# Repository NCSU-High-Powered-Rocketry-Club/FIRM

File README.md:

# FIRM

Filtered Inertial Rotation Module

FIRM is a project by the NCSU High Powered Rocketry Club to develop a flight computer for high powered rockets. The flight computer is designed to provide accurate attitude and position data during flight using an array of sensors and an error-state Kalman filter.

It is also designed to be modular and easily adaptable to different rocket configurations and mission requirements. The project includes a custom PCB that integrates the sensors and microcontroller into a compact, lightweight package suitable for high-speed flight.

This repository holds the STM32 firmware (written in C), a USB client (Rust, with Python and TypeScript bindings) that interfaces with the hardware, a React web app for Web Serial configuration, MkDocs documentation, and post-flight processing tools for log archives, ESKF replay, and trace analysis.

## Layout

| Path           | What it is                                                                   |
|----------------|------------------------------------------------------------------------------|
| `STM32/`       | Firmware (CubeMX / VS Code STM32 extension)                                  |
| `client/`      | USB client crates, `firm-client` Python bindings, and WASM/TypeScript client |
| `web/`         | React web app (Web Serial UI); depends on the local `client/` package        |
| `docs/`        | MkDocs documentation (Material theme), built from `mkdocs.yaml`              |
| `processing/`  | Offline tools: `firm-hprc` (`firm.flight_data`, `firm.eskf_lab`)             |
| `flight_data/` | Versioned flight-log archive (data only)                                     |
| `tests/`       | Pytest and protocol C checks (firmware unit tests live in `STM32/tests/`)    |

## Setup

Install [uv](https://docs.astral.sh/uv/), Rust, CMake, Ninja, a host C compiler, and [just](https://github.com/casey/just). Building the firmware (`just build`, `just build-firmware`, `just ci`) also needs the ARM GNU toolchain (`arm-none-eabi-gcc`) on your `PATH`. It comes with [STM32CubeCLT](https://www.st.com/en/development-tools/stm32cubeclt.html) (see [STM32/README.md](STM32/README.md)), or you can install the [Arm GNU Toolchain](https://developer.arm.com/downloads/-/arm-gnu-toolchain-downloads) directly (CI uses 13.3.Rel1).

`just` is a command runner, so every `just <recipe>` below needs it on your `PATH`. Once uv is installed, the easiest way to get it on any OS is:

```bash
uv tool install rust-just
```

Other options are `brew install just` (macOS), `winget install Casey.Just` (Windows), or `cargo install just`. See the [just install docs](https://just.systems/man/en/packages.html) for more.

Clone the repo and sync Python packages:

```bash
git clone https://github.com/NCSU-High-Powered-Rocketry-Club/FIRM.git
cd FIRM
just sync
```

`just sync` installs `firm-hprc` and `firm-client` into your `.venv`.

## Commands

```bash
just build          # firmware Debug ELF + native ESKF and C tests + cargo
just build-eskf     # only the native ESKF replay tool
just test           # CTest + cargo + pytest, excluding integration (summary at the end)
just lint           # ruff, rustfmt, clippy, clang-format
just ci             # local firmware/C tests/rust/python/lint
just publish        # PyPI + npm + crates.io (see `just dry_run=true publish`)
just --list         # list all just recipes including building/testing/linting individual targets
```

## Web app and docs

The React app in `web/` talks to FIRM over Web Serial and uses the local WASM client (`firm-client` from `client/`; the root `package.json` makes `client/` and `web/` one npm workspace). The MkDocs site lives in `docs/`. The app needs [Node.js](https://nodejs.org/) (version in `.nvmrc`) and `wasm-pack` (so `client/` can compile its WASM package); docs need only uv.

```bash
just sync-web       # npm ci for the workspace; builds client WASM + TypeScript (once, and after dependency changes)
just web-dev        # Vite dev server for the web app (http://localhost:5173/)
just build-web      # production build of the React app
just lint-web       # ESLint and Prettier over client/ and web/, tsc over web/
just build-docs     # MkDocs site to ./site/
```

`just web-dev` runs `npm run dev -w web`. `just build-docs` writes the static site to `site/`; `uv run --group docs mkdocs serve` serves it at http://127.0.0.1:8000/docs/. Production is https://firm.ncsurocketry.org/ (app) and https://firm.ncsurocketry.org/docs/ (docs). See [web/README.md](web/README.md).

## Processing tools

After running `just sync`:

```bash
uv run firm-log --help
uv run firm-eskf --help
uv run firm-trace --help
uv run firm-reconstruct --help
```

For live USB data from a connected FIRM, use `firm_client.FIRMClient`. See [client/README.md](client/README.md).

## Hardware

| Part Number   | Description          | Datasheet                                                                                                   |
|---------------|----------------------|-------------------------------------------------------------------------------------------------------------|
| ICM-45686     | 6 Axis IMU           | [Datasheet](https://www.mouser.com/catalog/specsheets/TDK_DS_000577_ICM_45686.pdf)                          |
| STM32F405RGT6 | Microcontroller      | [Datasheet](https://www.st.com/resource/en/datasheet/dm00037051.pdf)                                        |
| MMC5983MA     | Magnetometer         | [Datasheet](https://media.digikey.com/pdf/Data%20Sheets/MEMSIC%20PDFs/MMC5983MA_RevA_4-3-19.pdf)            |
| BMP581        | Pressure Sensor      | [Datasheet](https://www.bosch-sensortec.com/media/boschsensortec/downloads/datasheets/bst-bmp581-ds004.pdf) |
| ADXL371       | High-g Accelerometer | [Datasheet](https://www.analog.com/media/en/technical-documentation/data-sheets/adxl371.pdf)                |
| W25Q128JV     | 128 Mbit SPI Flash   | [Datasheet](https://www.winbond.com/resource-files/w25q128jv%20revf%2003272018%20plus.pdf)                  |

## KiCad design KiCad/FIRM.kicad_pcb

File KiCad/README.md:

# FIRM PCB
This README aims to explain the hardware of FIRM in-depth and explain the design choices that went into designing our board.

## Overview

The purpose of creating our own PCB for FIRM was for a few main reasons. A big reason is customizabiltiy. When creating a flight controller from breakout boards, we are largely limited by the breakout boards that are supplied by major hobbyist companies like Adafruit and Sparkfun. A second reason is size. It's no surprise that when you only buy the sensor itself and not the entire breakout board, you can save a lot of wasted space that otherwise would be taken up by standard 0.1 inch pitch pinouts. The last major reason is cost. Hobbyist companies put huge mark-ups on their breakout boards, so we save a lot of money by designing and ordering the boards ourselves.

The schematic design is split up into 4 major components:
- Microcontroller: The heart of the board, supplies all of our pinouts and programmed to interface with the sensors
- Sensors: The hardware units that read pressure, temperature, acceleration, angular rate, magnetic field, etc.
- Logging/Storage: Encompasses our flash chip and the microSD card socket
- Power: The power input for the board through either input pins or USB, as well as the voltage regulator

## Microcontroller

Our MCU is the STM32F405RGT6. The name of this chip tells us a lot of information about it:

- "STM32": This is the 32-bit MCU family. The other main example is STM8 for 8-bit MCUs.
- "F": The type of the MCU, F is for foundational, sometimes high-performance though. Thier naming scheme isn't super consistant. Other common ones are G for mainstream, L for low-power, H for high-performance, and W for wireless.
- "4": The core, specifies the ARM Cortex chip used. STM32F4 MCU's use an ARM Cortex M4.
- "05": One of the models in the STM32F4 product lineup
- "R": Number of pinouts on the MCU. R either means 64 or 66. In our case, we have 64 pinouts.
- "G": Flash memory size, we have 1024 KBytes.
- "T": Package type, T is for LQFP packages.
- "6": Temperature rating, 6 denotes -40\deg C to 105\deg C.
[Heres a guide with more information about the naming scheme](https://www.digikey.com/en/maker/tutorials/2020/understanding-stm32-naming-conventions)

The main reason we chose this MCU in particular was due to its popularity, namely in drone flight controllers. We decided that having an MCU that was well-documented was going to be more important than an MCU that had the best specs. While specs do matter, we started this project with no STM32 experience and we knew development would go faster when there's already someone online that has encountered (and fixed) all the issues we run into.

The pinouts are also important for the MCU. We wanted to communicate through our sensors through SPI, which is much faster than the alternative communication protocol, I2C. Another supported protocol is UART, which will be used (in future FIRM iterations) for GPS, and also can be used for communicating with a main device such as an Arduino so that FIRM can transmit flight data real-time to it. It is important to note that many of the pins have alternate uses and can be configred via STM32CubeMX to do different functions.

## Sensors

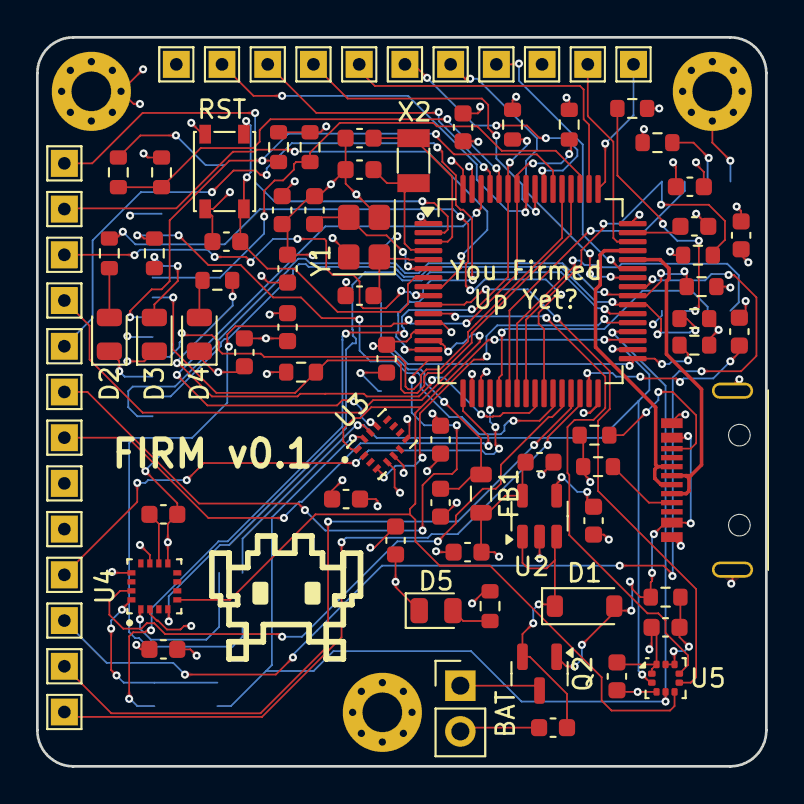
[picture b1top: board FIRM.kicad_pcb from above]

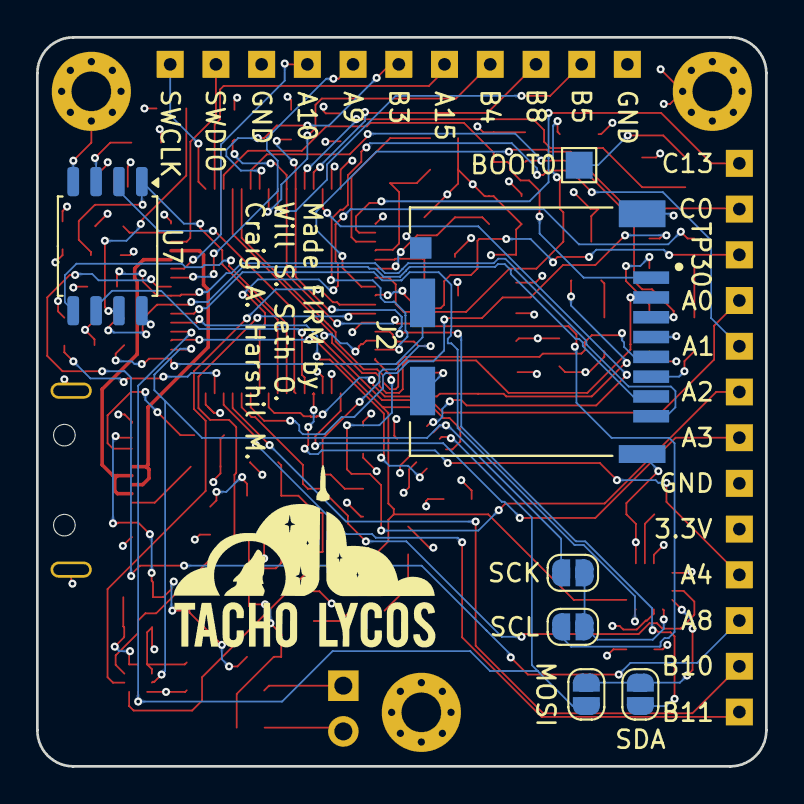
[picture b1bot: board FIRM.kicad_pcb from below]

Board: 4 copper layers, 40.5 x 40.5 mm, 98 parts (7 on the bottom side), 74 nets.

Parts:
3.3V: 3.3V Test Point; TestPoint_THTPad_1.5x1.5mm_Drill0.7mm
A0: PA0 Test Point; TestPoint_THTPad_1.5x1.5mm_Drill0.7mm
A1: PA1 Test Point; TestPoint_THTPad_1.5x1.5mm_Drill0.7mm
A2: PA2 Test Point; TestPoint_THTPad_1.5x1.5mm_Drill0.7mm
A3: PA3 Test Point; TestPoint_THTPad_1.5x1.5mm_Drill0.7mm
A4: PA4 Test Point; TestPoint_THTPad_1.5x1.5mm_Drill0.7mm
A8: PA8 Test Point; TestPoint_THTPad_1.5x1.5mm_Drill0.7mm
A9: PA9 Test Point; TestPoint_THTPad_1.5x1.5mm_Drill0.7mm
A10: PA10 Test Point; TestPoint_THTPad_1.5x1.5mm_Drill0.7mm
A15: PA15 Test Point; TestPoint_THTPad_1.5x1.5mm_Drill0.7mm
B3: PB3 Test Point; TestPoint_THTPad_1.5x1.5mm_Drill0.7mm
B4: PB4 Test Point; TestPoint_THTPad_1.5x1.5mm_Drill0.7mm
B5: PB5 Test Point; TestPoint_THTPad_1.5x1.5mm_Drill0.7mm
B8: PB8 Test Point; TestPoint_THTPad_1.5x1.5mm_Drill0.7mm
B10: PB10 Test Point; TestPoint_THTPad_1.5x1.5mm_Drill0.7mm
B11: PB11 Test Point; TestPoint_THTPad_1.5x1.5mm_Drill0.7mm
BAT: Conn_01x02_Pin; PinHeader_1x02_P2.54mm_Vertical
BOOT0: BOOT0 Pad; TestPoint_Pad_1.5x1.5mm
C0: PC0 Test Point; TestPoint_THTPad_1.5x1.5mm_Drill0.7mm
C1, C2, C3, C4, C5, C19, C20, C21, C25, C26, C27: 100n; C_0603_1608Metric
C6: 4u7; C_0603_1608Metric
C7: 10n; C_0603_1608Metric
C8, C15: 0.1u; C_0603_1608Metric
C9, C10: 2u2; C_0603_1608Metric
C11, C12: 6p; C_0603_1608Metric
C13: PC13 Test Point; TestPoint_THTPad_1.5x1.5mm_Drill0.7mm
C13#2, C14: 14p; C_0603_1608Metric
C16, C18: 1u; C_0603_1608Metric
C17, C22, C24: 10u; C_0603_1608Metric
C23: 470p; C_0603_1608Metric
D1: D_Schottky; D_SOD-123
D2, D3, D4, D5: LED; LED_0805_2012Metric
FB1: 120 Ohms @ 100 MHz; L_0805_2012Metric
GND: GND Test Point; TestPoint_THTPad_1.5x1.5mm_Drill0.7mm
GND#2: GND Through-Hole; TestPoint_THTPad_1.5x1.5mm_Drill0.7mm
GND#3: GND Test Point; TestPoint_THTPad_1.5x1.5mm_Drill0.7mm
H1, H2, H3: MountingHole_Pad; MountingHole_2.2mm_M2_Pad_Via
J2: DM3CS-SF; HRS_DM3CS-SF
MOSI: SPI_SDI; SolderJumper-2_P1.3mm_Open_RoundedPad1.0x1.5mm
Q2: IRLML6402; SOT-23
R1, R8: 100k; R_0603_1608Metric
R2, R3, R4, R5, R6: 47k; R_0603_1608Metric
R7, R13, R14, R21: 10k; R_0603_1608Metric
R9, R22: 5.1k; R_0603_1608Metric
R10: 330; R_0603_1608Metric
R11, R15: 1k2; R_0603_1608Metric
R12: 1k5; R_0603_1608Metric
R18, R19: 2k2; R_0603_1608Metric
R20: 100; R_0603_1608Metric
RST: PTS815; SW_SPST_PTS810
SCK: SPI_SCK; SolderJumper-2_P1.3mm_Open_RoundedPad1.0x1.5mm
SCL: I2C_SCL; SolderJumper-2_P1.3mm_Open_RoundedPad1.0x1.5mm
SDA: I2C_SDA; SolderJumper-2_P1.3mm_Open_RoundedPad1.0x1.5mm
SWCLK: SWCLK Through-Hole; TestPoint_THTPad_1.5x1.5mm_Drill0.7mm
SWDIO: SWDIO Through-Hole; TestPoint_THTPad_1.5x1.5mm_Drill0.7mm
TP30: PC1 Test Point; TestPoint_THTPad_1.5x1.5mm_Drill0.7mm
U1: STM32F405RGTx; LQFP-64_10x10mm_P0.5mm
U2: MIC5219-3.3YM5; SOT-23-5
U3: IC_ICM-45686
U4: IC_MMC5983MA
U5: ST_HLGA-10_2x2mm_P0.5mm_LayoutBorder3x2y
U6: A-USBC-20F0-EA-GSR05
U7: W25Q128JVS; SOIC-8_5.3x5.3mm_P1.27mm
X2: 32.768khz; Crystal_SMD_3215-2Pin_3.2x1.5mm
Y1: 12 MHz; Crystal_SMD_Abracon_ABM8G-4Pin_3.2x2.5mm

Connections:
+3.3V: 3.3V.1, C1.1, C2.1, C3.1, C4.1, C5.1, C6.1, C16.1, C18.1, C19.1, C20.1, C21.2, C24.1, C25.1, C26.2, C27.2, FB1.2, J2.4 (VDD), R2.2, R3.2, R4.2, R5.2, R6.2, R7.1, R13.1, R14.1, R15.2, R18.2, R19.2, R21.1, U1.1 (VBAT), U1.19 (VDD), U1.32 (VDD), U1.48 (VDD), U1.64 (VDD), U2.5 (OUT), U3.5 (VDDIO), U3.8 (VDD), U4.2 (VDD), U4.13 (VDDIO), U5.1 (VDDIO), U5.10 (VDD), U7.8 (VCC)
/BMP_CS: U1.10 (PC2), U5.6 (CSB)
/BMP_INT: U1.11 (PC3), U5.7 (INT)
/BOOT0: R1.1, R20.2, U1.60 (BOOT0)
/DBUG_0: R10.2, U1.26 (PB0)
/DBUG_1: R11.2, U1.27 (PB1)
/DBUG_2: R12.2, U1.25 (PC5)
/FLASH_CS: R21.2, U1.24 (PC4), U7.1 (~CS)
/HSE_IN: C13#2.1, U1.5 (PH0), Y1.1
/HSE_OUT: C14.1, U1.6 (PH1), Y1.3
/I2C1_SCL: R18.1, SCL.2 (B), U1.58 (PB6)
/I2C1_SDA: R19.1, SDA.2 (B), U1.59 (PB7)
/IMU_CS: U1.62 (PB9), U3.12 (AP_CS)
/IMU_INT: U1.37 (PC6), U3.4 (INT1/INT)
/LSE_IN: C11.1, U1.3 (PC14), X2.1
/LSE_OUT: C12.1, U1.4 (PC15), X2.2
/MAG_CS: U1.38 (PC7), U4.4 (SPI_CS)
/MAG_INT: U1.28 (PB2), U4.15 (INT)
/MISO1: U1.22 (PA6), U7.2 (DO/IO_{1})
/MISO2: U1.35 (PB14), U3.1 (AP_SDO/AP_AD0), U4.5 (SPI_SDO), U5.5 (SDO)
/MOSI1: U1.23 (PA7), U7.5 (DI/IO_{0})
/MOSI2: MOSI.2 (B), U1.36 (PB15), U3.14 (AP_SDA/APSDIO/APSDI), U5.4 (SDI)
/NRST: C15.1, RST.1, U1.7 (NRST)
/PA0: A0.1, U1.14 (PA0)
/PA1: A1.1, U1.15 (PA1)
/PA2: A2.1, U1.16 (PA2)
/PA3: A3.1, U1.17 (PA3)
/PA4: A4.1, U1.20 (PA4)
/PA8: A8.1, U1.41 (PA8)
/PA9: A9.1, U1.42 (PA9)
/PA10: A10.1, U1.43 (PA10)
/PA15: A15.1, U1.50 (PA15)
/PB3: B3.1, U1.55 (PB3)
/PB4: B4.1, U1.56 (PB4)
/PB5: B5.1, U1.57 (PB5)
/PB8: B8.1, U1.61 (PB8)
/PB10: B10.1, U1.29 (PB10)
/PB11: B11.1, U1.30 (PB11)
/PC0: C0.1, U1.8 (PC0)
/PC1: TP30.1, U1.9 (PC1)
/PC13: C13.1, U1.2 (PC13)
/SCK1: U1.21 (PA5), U7.6 (CLK)
/SCK2: SCK.2 (B), U1.34 (PB13), U3.13 (AP_SCL/AP_SCLK), U5.2 (SCK)
/SDIO_CK: J2.5 (CLK), U1.53 (PC12)
/SDIO_CMD: J2.3 (CMD), R4.1, U1.54 (PD2)
/SDIO_D0: J2.7 (DAT0), R5.1, U1.39 (PC8)
/SDIO_D1: J2.8 (DAT1), R6.1, U1.40 (PC9)
/SDIO_D2: J2.1 (DAT2), R2.1, U1.51 (PC10)
/SDIO_D3: J2.2 (CD/DAT3), R3.1, U1.52 (PC11)
/SD_DETECT: J2.9 (CD_SW), R7.2, U1.33 (PB12)
/SWCLK: SWCLK.1, U1.49 (PA14)
/SWDIO: SWDIO.1, U1.46 (PA13)
/USB_D+: U1.45 (PA12), U6.A6 (D+), U6.B6 (D+)
/USB_D-: U1.44 (PA11), U6.A7 (D-), U6.B7 (D-)
/VCAP1: C9.1, U1.31 (VCAP_1)
/VCAP2: C10.1, U1.47 (VCAP_2)
GND: BAT.2, C1.2, C2.2, C3.2, C4.2, C5.2, C6.2, C7.2, C8.2, C9.2, C10.2, C11.2, C12.2, C13#2.2, C14.2, C15.2, C16.2, C17.1, C18.2, C19.2, C20.2, C21.1, C22.2, C23.2, C24.2, C25.2, C26.1, C27.1, D2.1 (K), D3.1 (K), D4.1 (K), D5.1 (K), GND.1, GND#2.1, GND#3.1, H1.1, H2.1, H3.1, J2.6 (VSS), J2.S1 (GND), J2.S2 (GND), J2.S3 (GND), J2.S5 (GND), R1.2, R8.2, R9.2, R22.2, RST.2, U1.12 (VSSA), U1.18 (VSS), U1.63 (VSS), U2.2 (GND), U3.6 (GND), U4.9 (GND), U4.11 (GND), U5.3 (VSS), U5.8 (VSS), U5.9 (VSS), U6.A1 (GND), U6.B1 (GND), U6.S1 (SHIELD), U7.4 (GND), Y1.2, Y1.4
unnamed: C22.1, D1.1 (K), Q2.2 (S), U2.1 (IN), U2.3 (EN)
unnamed: D2.2 (A), R10.1
unnamed: D3.2 (A), R11.1
unnamed: D4.2 (A), R12.1
unnamed: D5.2 (A), R15.1
unnamed: MOSI.1 (A), SDA.1 (A), U4.16 (SDA/ SPI_SDI)
unnamed: SCK.1 (A), SCL.1 (A), U4.1 (SCL/ SPI_SCK)
unnamed: BOOT0.1, R20.1
unnamed: C7.1, C8.1, FB1.1, U1.13 (VDDA)
unnamed: C23.1, U2.4 (BP)
unnamed: C17.2, U4.10 (CAP)
unnamed: R9.1, U6.A5 (CC1)
unnamed: R22.1, U6.B5 (CC2)
unnamed: R13.2, U7.7 (~HOLD/~RESET/IO_{3})
unnamed: R14.2, U7.3 (~WP/IO_{2})
VBAT: BAT.1, Q2.3 (D)
VBUS: D1.2 (A), Q2.1 (G), R8.1, U6.A4 (VBUS), U6.B4 (VBUS)

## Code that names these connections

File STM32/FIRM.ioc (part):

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Mcu.Name=STM32F405RGTx
Mcu.Package=LQFP64
Mcu.UserName=STM32F405RGTx
PA10.Mode=Asynchronous
PA10.Signal=USART1_RX
PA11.Mode=Device_Only
PA11.Signal=USB_OTG_FS_DM
PA12.Mode=Device_Only
PA12.Signal=USB_OTG_FS_DP
PA13.Mode=Serial_Wire
PA13.Signal=SYS_JTMS-SWDIO
PA14.Mode=Serial_Wire
PA14.Signal=SYS_JTCK-SWCLK
PA4.GPIOParameters=GPIO_PuPd,GPIO_Label
PA4.GPIO_Label=CONF_CHECK
PA4.GPIO_PuPd=GPIO_PULLUP
PA4.Signal=GPIO_Input
PA5.GPIOParameters=GPIO_Speed,GPIO_PuPd
PA5.GPIO_PuPd=GPIO_NOPULL
PA5.GPIO_Speed=GPIO_SPEED_FREQ_HIGH
PA5.Mode=Full_Duplex_Master
PA5.Signal=SPI1_SCK
PA6.GPIOParameters=GPIO_Speed,GPIO_PuPd
PA6.GPIO_PuPd=GPIO_NOPULL
PA6.GPIO_Speed=GPIO_SPEED_FREQ_HIGH
PA6.Mode=Full_Duplex_Master
PA6.Signal=SPI1_MISO
PA7.GPIOParameters=GPIO_Speed,GPIO_PuPd
PA7.GPIO_PuPd=GPIO_NOPULL
PA7.GPIO_Speed=GPIO_SPEED_FREQ_HIGH
PA7.Mode=Full_Duplex_Master
PA7.Signal=SPI1_MOSI
PA8.GPIOParameters=GPIO_Label
PA8.GPIO_Label=ADXL371_CS
PA8.Signal=GPIO_Output
PA9.Mode=Asynchronous
PA9.Signal=USART1_TX
PB0.GPIOParameters=GPIO_Label,GPIO_ModeDefaultEXTI
PB0.GPIO_Label=ICM45686_Interrupt
PB0.GPIO_ModeDefaultEXTI=GPIO_MODE_IT_FALLING
PB0.Signal=GPXTI0
PB1.GPIOParameters=GPIO_Label,GPIO_ModeDefaultEXTI
PB1.GPIO_Label=ADXL371_Interrupt
PB1.GPIO_ModeDefaultEXTI=GPIO_MODE_IT_FALLING
PB1.Signal=GPXTI1
PB10.Mode=I2C
PB10.Signal=I2C2_SCL
PB11.Mode=I2C
PB11.Signal=I2C2_SDA
PB12.Signal=GPIO_Input
PB13.GPIOParameters=GPIO_Speed,GPIO_PuPd
PB13.GPIO_PuPd=GPIO_NOPULL
PB13.GPIO_Speed=GPIO_SPEED_FREQ_HIGH
PB13.Mode=Full_Duplex_Master
PB13.Signal=SPI2_SCK
PB14.GPIOParameters=GPIO_Speed,GPIO_PuPd
PB14.GPIO_PuPd=GPIO_NOPULL
PB14.GPIO_Speed=GPIO_SPEED_FREQ_HIGH
PB14.Mode=Full_Duplex_Master
PB14.Signal=SPI2_MISO
PB15.GPIOParameters=GPIO_Speed,GPIO_PuPd
PB15.GPIO_PuPd=GPIO_NOPULL
PB15.GPIO_Speed=GPIO_SPEED_FREQ_HIGH
PB15.Mode=Full_Duplex_Master
PB15.Signal=SPI2_MOSI
PB2.GPIOParameters=GPIO_PuPd,GPIO_Label,GPIO_ModeDefaultEXTI
PB2.GPIO_Label=MMC5983MA_Interrupt
PB2.GPIO_ModeDefaultEXTI=GPIO_MODE_IT_RISING
PB2.GPIO_PuPd=GPIO_PULLDOWN
PB2.Signal=GPXTI2
PB3.Mode=Full_Duplex_Master
PB3.Signal=SPI3_SCK
PB4.Mode=Full_Duplex_Master
PB4.Signal=SPI3_MISO
PB5.Mode=Full_Duplex_Master
PB5.Signal=SPI3_MOSI
PB6.GPIOParameters=GPIO_Speed,GPIO_Pu,GPIO_Mode
PB6.GPIO_Mode=GPIO_MODE_AF_OD
PB6.GPIO_Pu=GPIO_PULLUP
PB6.GPIO_Speed=GPIO_SPEED_FREQ_VERY_HIGH
PB6.Mode=I2C
PB6.Signal=I2C1_SCL
PB7.GPIOParameters=GPIO_Speed,GPIO_Pu,GPIO_Mode
PB7.GPIO_Mode=GPIO_MODE_AF_OD
PB7.GPIO_Pu=GPIO_PULLUP
PB7.GPIO_Speed=GPIO_SPEED_FREQ_VERY_HIGH
PB7.Mode=I2C
PB7.Signal=I2C1_SDA
PB8.GPIOParameters=GPIO_Label
PB8.GPIO_Label=DEBUG1
PB8.Signal=GPIO_Output
PB9.GPIOParameters=GPIO_Label
PB9.GPIO_Label=ICM45686_CS
PB9.Signal=GPIO_Output
PC0.Signal=GPIO_Output
PC1.GPIOParameters=GPIO_Label
PC1.GPIO_Label=DEBUG0
PC1.Signal=GPIO_Output
PC10.GPIOParameters=GPIO_PuPd,GPIO_Speed_High_Default
PC10.GPIO_PuPd=GPIO_PULLUP
PC10.GPIO_Speed_High_Default=GPIO_SPEED_FREQ_HIGH
PC10.Mode=SD_4_bits_Wide_bus
PC10.Signal=SDIO_D2
PC11.GPIOParameters=GPIO_Speed_High_Default
PC11.GPIO_Speed_High_Default=GPIO_SPEED_FREQ_HIGH
PC11.Mode=SD_4_bits_Wide_bus
PC11.Signal=SDIO_D3
PC12.GPIOParameters=GPIO_Speed_High_Default
PC12.GPIO_Speed_High_Default=GPIO_SPEED_FREQ_HIGH
PC12.Mode=SD_4_bits_Wide_bus
PC12.Signal=SDIO_CK
PC2.GPIOParameters=GPIO_PuPd,GPIO_Label
PC2.GPIO_Label=BMP581_CS
PC2.GPIO_PuPd=GPIO_PULLUP
PC2.Signal=GPIO_Output
PC3.GPIOParameters=GPIO_PuPd,GPIO_Label,GPIO_ModeDefaultEXTI
PC3.GPIO_Label=BMP581_Interrupt
PC3.GPIO_ModeDefaultEXTI=GPIO_MODE_IT_FALLING
PC3.GPIO_PuPd=GPIO_NOPULL
PC3.Signal=GPXTI3
PC4.GPIOParameters=GPIO_Label
PC4.GPIO_Label=FLASH_CS
PC4.Signal=GPIO_Output
PC5.GPIOParameters=GPIO_Label
PC5.GPIO_Label=DEBUG2
PC5.Signal=GPIO_Output
PC7.GPIOParameters=GPIO_PuPd,GPIO_Label
PC7.GPIO_Label=MMC5983MA_CS
PC7.GPIO_PuPd=GPIO_PULLUP
PC7.Signal=GPIO_Output
PC8.GPIOParameters=GPIO_PuPd,GPIO_Speed_High_Default
PC8.GPIO_PuPd=GPIO_PULLUP
PC8.GPIO_Speed_High_Default=GPIO_SPEED_FREQ_HIGH
PC8.Mode=SD_4_bits_Wide_bus
PC8.Signal=SDIO_D0
PC9.GPIOParameters=GPIO_PuPd,GPIO_Speed_High_Default
PC9.GPIO_PuPd=GPIO_PULLUP
PC9.GPIO_Speed_High_Default=GPIO_SPEED_FREQ_HIGH
PC9.Mode=SD_4_bits_Wide_bus
PC9.Signal=SDIO_D1
PD2.GPIOParameters=GPIO_PuPd,GPIO_Speed_High_Default
PD2.GPIO_PuPd=GPIO_PULLUP
PD2.GPIO_Speed_High_Default=GPIO_SPEED_FREQ_HIGH
PD2.Mode=SD_4_bits_Wide_bus
PD2.Signal=SDIO_CMD
PH0-OSC_IN.Mode=HSE-External-Oscillator
PH0-OSC_IN.Signal=RCC_OSC_IN
PH1-OSC_OUT.Mode=HSE-External-Oscillator
PH1-OSC_OUT.Signal=RCC_OSC_OUT
RCC.HSE_VALUE=12000000
RCC.SYSCLKFreq_VALUE=168000000
RCC.SYSCLKSource=RCC_SYSCLKSOURCE_PLLCLK
board=custom

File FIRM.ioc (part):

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Mcu.Name=STM32F405RGTx
Mcu.Package=LQFP64
Mcu.UserName=STM32F405RGTx
PA11.Mode=Device_Only
PA11.Signal=USB_OTG_FS_DM
PA12.Mode=Device_Only
PA12.Signal=USB_OTG_FS_DP
PA13.Mode=Serial_Wire
PA13.Signal=SYS_JTMS-SWDIO
PA14.Mode=Serial_Wire
PA14.Signal=SYS_JTCK-SWCLK
PB10.Mode=I2C
PB10.Signal=I2C2_SCL
PB11.Mode=I2C
PB11.Signal=I2C2_SDA
PB12.Signal=GPIO_Input
PB13.GPIOParameters=GPIO_PuPd
PB13.GPIO_PuPd=GPIO_PULLDOWN
PB13.Mode=Full_Duplex_Master
PB13.Signal=SPI2_SCK
PB14.GPIOParameters=GPIO_PuPd
PB14.GPIO_PuPd=GPIO_NOPULL
PB14.Mode=Full_Duplex_Master
PB14.Signal=SPI2_MISO
PB15.GPIOParameters=GPIO_PuPd
PB15.GPIO_PuPd=GPIO_PULLDOWN
PB15.Mode=Full_Duplex_Master
PB15.Signal=SPI2_MOSI
PB3.Mode=Full_Duplex_Master
PB3.Signal=SPI3_SCK
PB4.Mode=Full_Duplex_Master
PB4.Signal=SPI3_MISO
PB5.Mode=Full_Duplex_Master
PB5.Signal=SPI3_MOSI
PB6.GPIOParameters=GPIO_Speed,GPIO_Pu,GPIO_Mode
PB6.GPIO_Mode=GPIO_MODE_AF_OD
PB6.GPIO_Pu=GPIO_PULLUP
PB6.GPIO_Speed=GPIO_SPEED_FREQ_VERY_HIGH
PB6.Mode=I2C
PB6.Signal=I2C1_SCL
PB7.GPIOParameters=GPIO_Speed,GPIO_Pu,GPIO_Mode
PB7.GPIO_Mode=GPIO_MODE_AF_OD
PB7.GPIO_Pu=GPIO_PULLUP
PB7.GPIO_Speed=GPIO_SPEED_FREQ_VERY_HIGH
PB7.Mode=I2C
PB7.Signal=I2C1_SDA
PB8.GPIOParameters=GPIO_Label,GPIO_ModeDefaultEXTI
PB8.GPIO_Label=Mag_Interrupt
PB8.GPIO_ModeDefaultEXTI=GPIO_MODE_IT_RISING
PB8.Signal=GPXTI8
PB9.GPIOParameters=GPIO_Label
PB9.GPIO_Label=IMU_CS
PB9.Signal=GPIO_Output
PC0.Signal=GPIO_Output
PC1.Signal=GPIO_Output
PC10.GPIOParameters=GPIO_PuPd
PC10.GPIO_PuPd=GPIO_PULLUP
PC10.Mode=SD_4_bits_Wide_bus
PC10.Signal=SDIO_D2
PC11.Mode=SD_4_bits_Wide_bus
PC11.Signal=SDIO_D3
PC12.Mode=SD_4_bits_Wide_bus
PC12.Signal=SDIO_CK
PC2.GPIOParameters=GPIO_Label
PC2.GPIO_Label=BMP581_CS
PC2.Signal=GPIO_Output
PC3.GPIOParameters=GPIO_PuPd,GPIO_Label,GPIO_ModeDefaultEXTI
PC3.GPIO_Label=BMP581_Interrupt
PC3.GPIO_ModeDefaultEXTI=GPIO_MODE_IT_FALLING
PC3.GPIO_PuPd=GPIO_NOPULL
PC3.Signal=GPXTI3
PC6.GPIOParameters=GPIO_Label,GPIO_ModeDefaultEXTI
PC6.GPIO_Label=IMU_Interrupt
PC6.GPIO_ModeDefaultEXTI=GPIO_MODE_IT_FALLING
PC6.Signal=GPXTI6
PC8.GPIOParameters=GPIO_PuPd
PC8.GPIO_PuPd=GPIO_PULLUP
PC8.Mode=SD_4_bits_Wide_bus
PC8.Signal=SDIO_D0
PC9.GPIOParameters=GPIO_PuPd
PC9.GPIO_PuPd=GPIO_PULLUP
PC9.Mode=SD_4_bits_Wide_bus
PC9.Signal=SDIO_D1
PD2.GPIOParameters=GPIO_PuPd
PD2.GPIO_PuPd=GPIO_PULLUP
PD2.Mode=SD_4_bits_Wide_bus
PD2.Signal=SDIO_CMD
PH0-OSC_IN.Mode=HSE-External-Oscillator
PH0-OSC_IN.Signal=RCC_OSC_IN
PH1-OSC_OUT.Mode=HSE-External-Oscillator
PH1-OSC_OUT.Signal=RCC_OSC_OUT
RCC.HSE_VALUE=12000000
RCC.SYSCLKFreq_VALUE=168000000
RCC.SYSCLKSource=RCC_SYSCLKSOURCE_PLLCLK
board=custom

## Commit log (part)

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2026-01-09 changed packet structure
2026-01-09 Wrote test for utils
2026-01-10 renamed fields
2026-01-10 start fsm
2026-01-10 fixed filter stack overflow and response packet size
2026-01-10 fsm logic
2026-01-11 led mode
2026-01-11 fixed kf
2026-01-11 fixed
2026-01-11 fixed commands
2026-01-12 change state to live
2026-01-12 added mock command
2026-01-12 progress
2026-01-13 new commands written, not tested yet
2026-01-13 added mock packets
2026-01-13 wrote a function to write mock settings to sector three of the flash chip. Next time I will try to write a general write function using enums to make it easier what you're writting. This function can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
2026-01-13 Fixed some some function declaration mistakes.
2026-01-13 fixed Syntax errors
2026-01-14 testing
2026-01-14 endianness
2026-01-14 endian
2026-01-14 Wrote an universal function for writting the settings to the flash chip. Using a enum it can write either to sector 0 or sector 3. init and mock respectfully.
2026-01-14 fixed errors
2026-01-14 Changed coding convention formatting.
2026-01-15 fixing flash
2026-01-15 working flash
2026-01-15 Removed a redundant function
2026-01-16 testing mock
2026-01-16 done?
2026-01-20 First draft of ADXL lib
2026-01-20 added migrator script
2026-01-20 Updated serial integer print function to include argument for new line
2026-01-20 updated decoder.py & logger.c
2026-01-21 start test
2026-01-22 slow parsing
2026-01-22 Finished adding the functionality for new line after printed usb debug float, int, or char.
2026-01-22 Fixed CmakeList
2026-01-22 Working on a Fifo write check
2026-01-22 debugging migrator.py & decoder.py
2026-01-22 Wrote Software Reset
2026-01-24 cooked
2026-01-24 write tests
2026-01-24 fix cmake
2026-01-25 Softreset status check added
2026-01-25 Updated to new firm client and added developer panel
2026-01-25 Clean up
2026-01-26 Set interrupt 1 to data ready
2026-01-26 Turned Active low for INT1
2026-01-26 attemptes to debug imu
2026-01-27 fixed imu breaking
2026-01-27 Disabled High pass and Low Pass filter
2026-01-27 Typo :(
2026-01-27 Starting measurement settings, Linkloop? autosleep? overrage?
2026-01-27 Changed usb_print_debug.h to also show the changes to the c file
2026-01-27 Disabled FIFO
2026-01-27 Working on adxl471
2026-01-27 Anothe type
2026-01-28 doesnt work
2026-01-28 added read data function
2026-01-29 Scale factor added. Working on ADXL371.h now
2026-01-29 A good stopping point before testing? (finished ADXL371.h)
2026-01-29 almost working
2026-01-29 ukf indentation
2026-01-29 Low noise operation!!!
2026-01-29 Soft reset reorder
2026-01-29 heheh
2026-01-29 Updated header changes, but haven't tested yet
2026-01-31 predict tests working
2026-01-31 kf working
2026-01-31 logger v1.2
2026-01-31 updated log name
2026-01-31 fixed version
2026-01-31 Fixed some typos and drafted data processing function
2026-02-01 wrote unit test for fsm
2026-02-01 updated migrator
2026-02-01 gitignore
2026-02-01 fixed file extension
2026-02-01 cleaned up the tests
2026-02-01 added tests for logger
2026-02-02 [pre-commit.ci] pre-commit autoupdate
    updates:
    - [github.com/astral-sh/ruff-pre-commit: v0.14.10 → v0.14.14](https://github.com/astral-sh/ruff-pre-commit/compare/v0.14.10...v0.14.14)
    - [github.com/cpp-linter/cpp-linter-hooks: v1.1.11 → v1.1.12](https://github.com/cpp-linter/cpp-linter-hooks/compare/v1.1.11...v1.1.12)
2026-02-03 mock
2026-02-03 good?
2026-02-03 Set up settings and data processing. Still need ot finish loop_firm
2026-02-04 delay ukf task
2026-02-04 removed cmsis
2026-02-04 set calibration command
2026-02-05 we are so back
2026-02-05 Added correct accel and gyro calibration
2026-02-05 Made a calibration panel
2026-02-05 Fix packets not sending when the USB is busy
2026-02-06 added cdc check
2026-02-06 holy shit it actually worked we're so back
2026-02-06 removed unecessary checks
2026-02-06 Add tracing
2026-02-06 Fix setting frequency
2026-02-06 tweaks
2026-02-06 fixed it fr this time
2026-02-06 robustness
2026-02-06 Set SD card back to 200Mb
2026-02-10 launch
2026-02-10 Makes the code require dtr before it starts transmitting
2026-02-10 Format files and fix pre-commit hook
2026-02-10 Fix pre-commit ci
2026-02-11 Add GetCalibration command
2026-02-11 formatting
2026-02-11 Update ioc to match project
2026-02-11 Regenerate usbd_cdc_if.c
2026-02-11 Fixed calibration code and added GetCalibration command
2026-02-11 Made calibration panel actually work
2026-02-12 cleanup
2026-02-12 Fixed some bugs and got pre-commit passing
2026-02-12 created "enum" array that holds LED bits
2026-02-13 Jump to Bootloader
    New command to allow a jump to the bootloader. Python script to test the bootloader jump command. A few LED flickers to indicate when entering flashed code and entering bootloader mode.
2026-02-14 Added write and read checks to setup
2026-02-14 new firm
2026-02-16 added high g logging
2026-02-17 Trying to fix include errors
2026-02-17 Test
2026-02-18 Add things
2026-02-18 Im goated
2026-02-18 slew rate
2026-02-20 dogshit
2026-02-20 Added check box to stop data packet bytes
2026-02-20 Polished the dev panel bytes
2026-02-20 Fix magnet buildup in MMC
2026-02-20 updated kf constants and state
2026-02-20 fuck me ig
2026-02-21 tune
2026-03-02 fixed boards
2026-03-02 [pre-commit.ci] pre-commit autoupdate
    updates:
    - [github.com/pre-commit/mirrors-clang-format: v21.1.8 → v22.1.0](https://github.com/pre-commit/mirrors-clang-format/compare/v21.1.8...v22.1.0)
    - [github.com/astral-sh/ruff-pre-commit: v0.14.10 → v0.15.4](https://github.com/astral-sh/ruff-pre-commit/compare/v0.14.10...v0.15.4)
    - [github.com/cpp-linter/cpp-linter-hooks: v1.1.11 → v1.1.13](https://github.com/cpp-linter/cpp-linter-hooks/compare/v1.1.11...v1.1.13)
2026-03-03 driver working, still need log header
2026-03-03 Fixed Build errors
2026-03-05 adxl log, settings, decoder, migrator updates
2026-03-05 Finished config, gonna work on read and write next
2026-03-09 reduce polling rate, fix kf for 1.0
2026-03-09 ready
2026-03-09 changed filename and comments
2026-03-09 file comment
2026-03-09 renamed adxl
2026-03-10 oops
2026-03-10 completely untested, rawdog code
2026-03-11 mock support and better filter init
2026-03-12 update firm-client
2026-03-12 progress, will finish after launch
2026-03-12 Revert "update firm-client"
2026-03-13 attempt at fixing vel
2026-03-13 fixed?
2026-03-13 unhardcode matrix
2026-03-13 decoder fix
2026-03-17 quick change to decoder csv
2026-03-17 fix board orientation comments
2026-03-21 filter done, need to test
2026-03-21 reset accum
2026-03-23 done
2026-03-23 fix adxl scale factor in header
2026-03-24 fix mock
2026-03-24 mock fix
2026-03-24 Attempted to fix read and write HAL functions
2026-03-24 fix mocks
2026-03-25 added script to set callibration values in frm file
2026-03-25 fix decoder and firmware version
2026-03-25 fix and gitignore yaml
2026-03-25 sensor orientation in mocks fix
2026-03-25 remove led
2026-03-25 log version check
2026-03-25 typo
2026-03-25 remove serial debug print
2026-03-26 Finished read function
2026-03-26 set up to test
2026-03-27 Fiex write and read HAl Functions??
2026-03-28 Was able to ge to kernel once. Having problems
2026-03-28 untested
2026-03-30 testing in progress
2026-03-30 tested
2026-03-30 removed default settings write
2026-03-31 Patched up read check bug
2026-03-31 add null checks
2026-03-31 removed decoder padding. updated migrator
2026-04-02 fixes
2026-04-03 Batch decoder and data analyzer .py added
2026-04-06 [pre-commit.ci] pre-commit autoupdate
    updates:
    - [github.com/pre-commit/mirrors-clang-format: v21.1.8 → v22.1.2](https://github.com/pre-commit/mirrors-clang-format/compare/v21.1.8...v22.1.2)
    - [github.com/astral-sh/ruff-pre-commit: v0.14.10 → v0.15.9](https://github.com/astral-sh/ruff-pre-commit/compare/v0.14.10...v0.15.9)
    - [github.com/cpp-linter/cpp-linter-hooks: v1.1.11 → v1.4.0](https://github.com/cpp-linter/cpp-linter-hooks/compare/v1.1.11...v1.4.0)
2026-04-06 abstract out rotation matrix
2026-04-06 remove firm python folder
2026-04-08 Finished batch_decoder. The code will put the processed files into folders labeled with the name of the processed log.
2026-04-08 updated ResponsePacket variable
2026-04-10 some scripts
2026-04-10 removed mag, need to test
2026-04-10 hopefully deleted and moved files correctly
2026-04-11 add firm-client
2026-04-11 [pre-commit.ci] auto fixes from pre-commit.com hooks
    for more information, see https://pre-commit.ci
2026-04-12 edit readme, verify rust code builds and tests pass
2026-04-13 added ADXL high g packets to client
2026-04-13 meta constants table
2026-04-16 tests wip
2026-04-16 unit tested sensors
2026-04-16 reformatting naming for structs, functions, etc. mostly from packet to snapshot
2026-04-17 beginning abstraction
2026-04-17 fix altitude zeroing
2026-04-18 sensor manager main logic
2026-04-18 tests for overflow counter
2026-04-19 fatfs driver, new logger file, logger storage, and target file linking
2026-04-19 some fixes, and test setup
2026-04-19 fake logger implementation for testing
2026-04-19 copilot tests but i think they are good tests
2026-04-19 suggested fix
2026-04-19 mocking ring buffer + tests
2026-04-19 wip, removing mock task, merging into usb task
2026-04-19 add hardware crc
2026-04-19 nvm im just deleting crc
2026-04-20 renaming a bunch and also usb task and command handling
2026-04-21 system commands
2026-04-27 fixing slop
2026-04-28 it compiles ig
2026-04-28 setup for tests
2026-04-28 INA219 Draft one
2026-05-04 [pre-commit.ci] pre-commit autoupdate
    updates:
    - [github.com/pre-commit/mirrors-clang-format: v21.1.8 → v22.1.4](https://github.com/pre-commit/mirrors-clang-format/compare/v21.1.8...v22.1.4)
    - [github.com/astral-sh/ruff-pre-commit: v0.14.10 → v0.15.12](https://github.com/astral-sh/ruff-pre-commit/compare/v0.14.10...v0.15.12)
    - [github.com/cpp-linter/cpp-linter-hooks: v1.1.11 → v1.4.0](https://github.com/cpp-linter/cpp-linter-hooks/compare/v1.1.11...v1.4.0)

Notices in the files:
README.md:
License: MIT
